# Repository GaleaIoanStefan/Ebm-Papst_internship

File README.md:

# Ebm-Papst_internship
This project contains the PCB design for a equipment that measures contact heat transfer rates.

# The Block Diagram of the Project

In here we can see the main parts of the project namely the supply, a feedback control loop of the ventilator and another feedback control loop of the metal plate. Everything that is contained in the colored frame sits on the actual PCB.

An Arduino Nano Esp32 microcontroller is the brain of the board, which will control the speed of the fan on the left of the schematic with a voltage switch, through a Hall speed sensor to complete a feedback loop. Similarly, on the right side, the esp32 will control the temperature of a hob with a 120W resistor with a voltage switch, and the feedback communication is done by 2 NTC thermistors

The tool used in this project was KiCad 9.0

# The electrical schematic of the PCB

# The layout of the PCB

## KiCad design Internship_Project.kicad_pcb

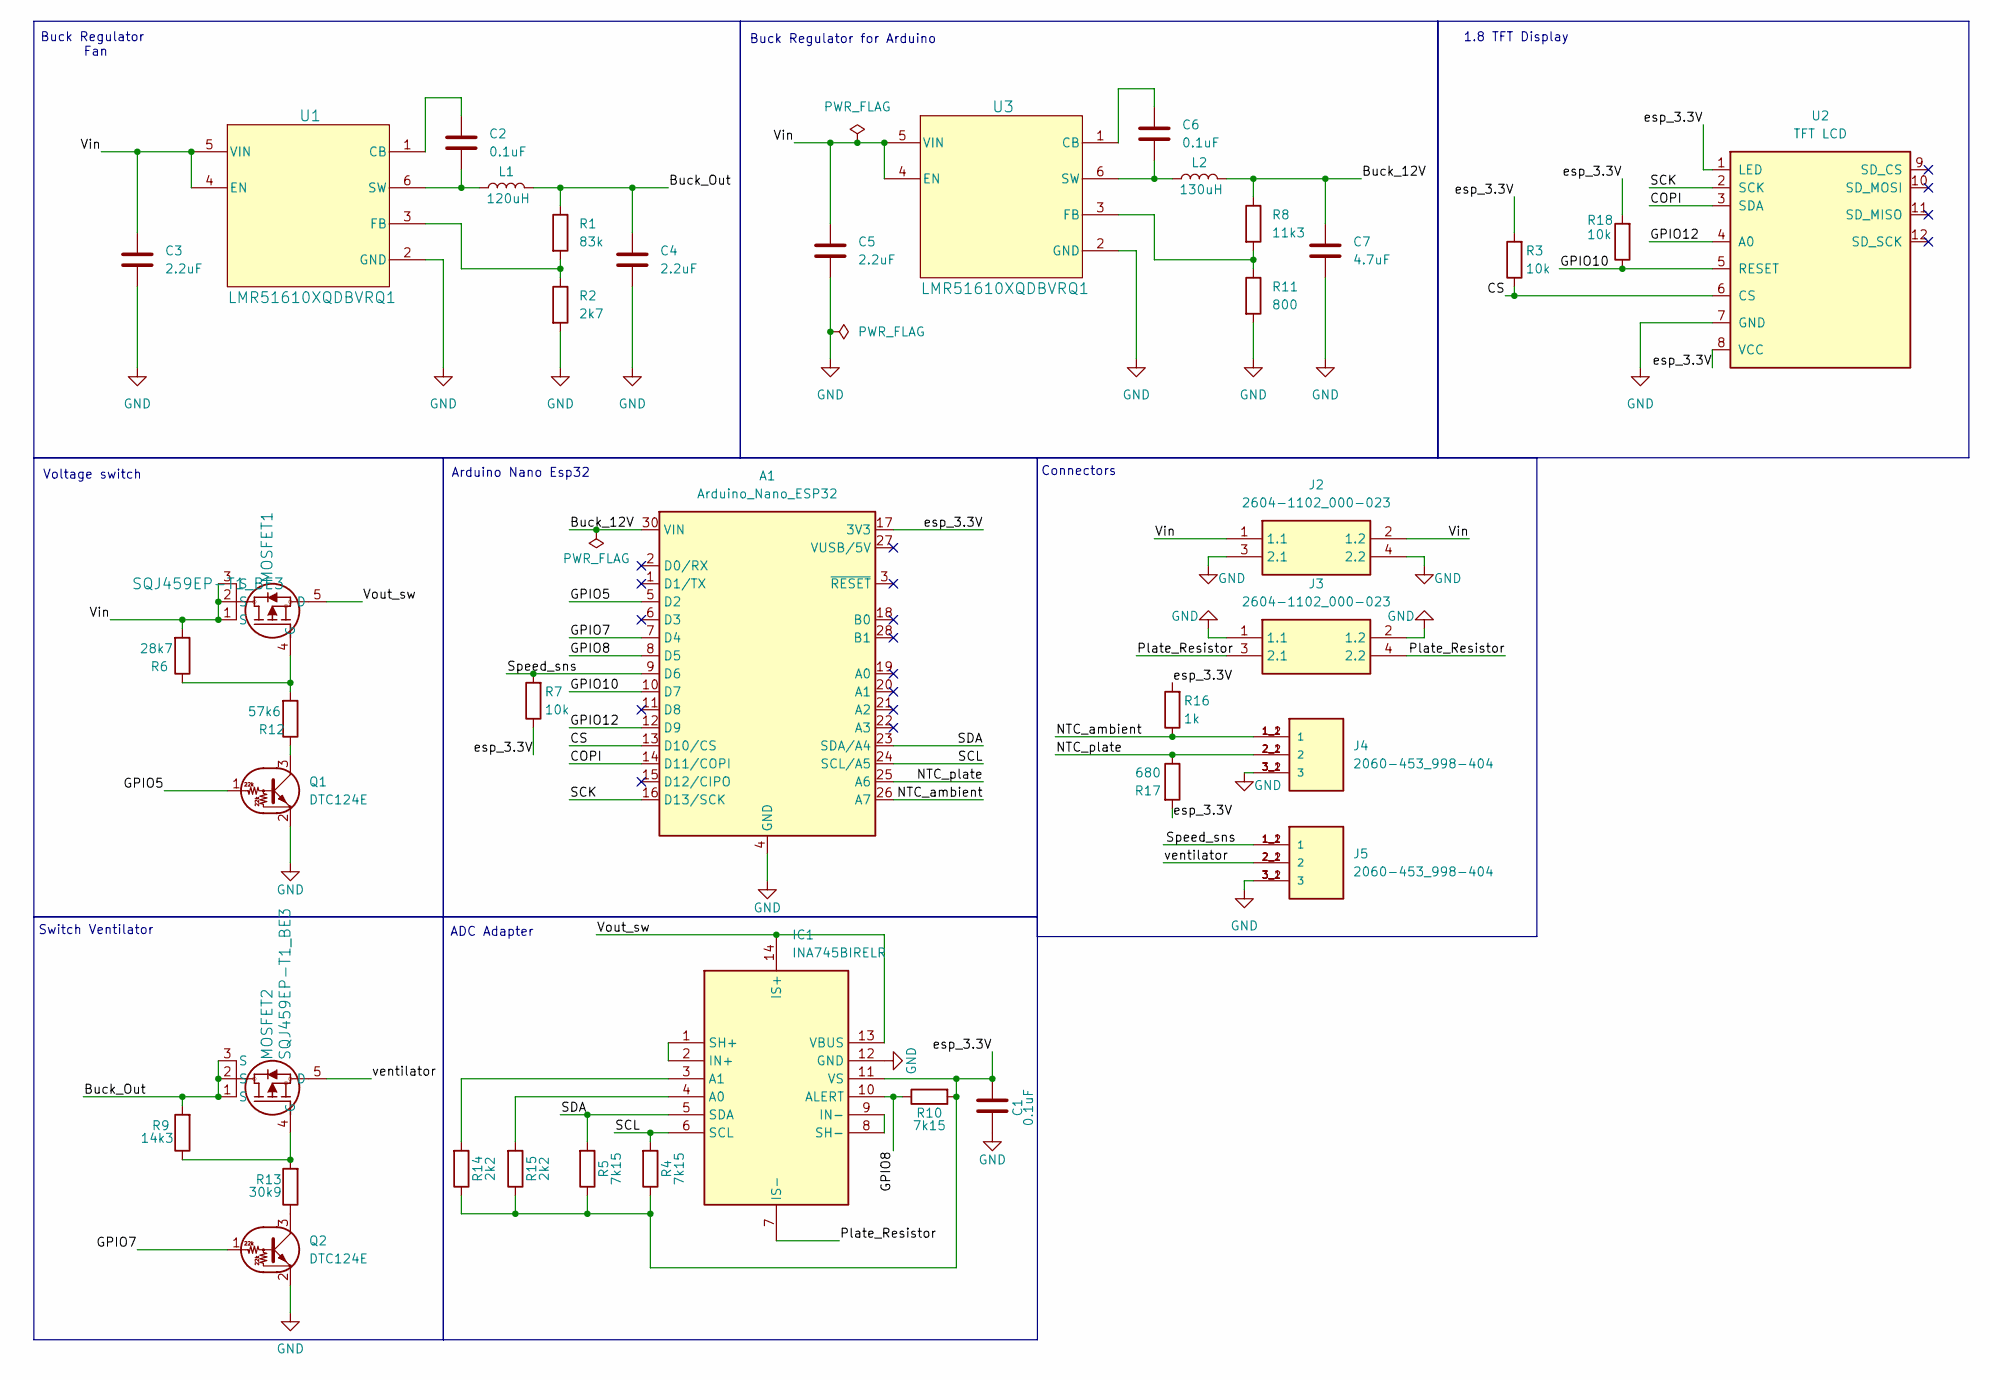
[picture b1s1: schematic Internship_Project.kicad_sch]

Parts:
A1: Arduino_Nano_ESP32; Arduino_Nano_WithMountingHoles
C1, C2, C6: 0.1uF; C_0805_2012Metric
C3, C4, C5: 2.2uF; C_1206_3216Metric
C7: 4.7uF; C_1206_3216Metric
IC1: INA745BIRELR; Manufacturer_Part_Number INA745BIRELR; Mouser Part Number 595-INA745BIRELR
J2, J3: 2604-1102_000-023; 26041102000023; Manufacturer_Part_Number 2604-1102/000-023
J4, J5: 2060-453_998-404; WAGO_2060-453_998-404; PARTREV N/A
L1: 120uH; L_1210_3225Metric
L2: 130uH; L_1210_3225Metric
MOSFET1, MOSFET2: SQJ459EP-T1_BE3; TO_0EP-T1_BE3_VIS
Q1, Q2: DTC124E; SOT-23
R1: 83k; R_0603_1608Metric
R2: 2k7; R_0603_1608Metric
R3, R7, R18: 10k; R_0603_1608Metric
R4, R5, R10: 7k15; R_0603_1608Metric
R6: 28k7; R_0603_1608Metric
R8: 11k3; R_0603_1608Metric
R9: 14k3; R_0603_1608Metric
R11: 800; R_0603_1608Metric
R12: 57k6; R_0603_1608Metric
R13: 30k9; R_0603_1608Metric
R14, R15: 2k2; R_0603_1608Metric
R16: 1k; R_0603_1608Metric
R17: 680; R_0603_1608Metric
U1, U3: LMR51610XQDBVRQ1; DBV0006A-IPC_A
U2: TFT LCD; TFT LCD 1.8inch 128x160 w_ SD Card Slot

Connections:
/Buck_12V: A1.30 (VIN), C7.1, L2.2, R8.1
/Buck_Out: C4.1, L1.2, MOSFET2.1 (S), MOSFET2.2 (S), MOSFET2.3 (S), R1.1, R9.2
/COPI: A1.14 (D11/COPI), U2.3 (SDA)
/CS: A1.13 (D10/CS), R3.1, U2.6 (CS)
/GPIO5: A1.5 (D2), Q1.1 (B)
/GPIO7: A1.7 (D4), Q2.1 (B)
/GPIO8: A1.8 (D5), IC1.10 (ALERT), R10.1
/GPIO10: A1.10 (D7), R18.1, U2.5 (RESET)
/GPIO12: A1.12 (D9), U2.4 (A0)
/NTC_ambient: A1.26 (A7), J4.1_1 (1), J4.1_2 (1), R16.1
/NTC_plate: A1.25 (A6), J4.2_1 (2), J4.2_2 (2), R17.1
/Plate_Resistor: IC1.7 (IS-), J3.3 (2.1), J3.4 (2.2)
/SCK: A1.16 (D13/SCK), U2.2 (SCK)
/SCL: A1.24 (SCL/A5), IC1.6 (SCL), R4.2
/SDA: A1.23 (SDA/A4), IC1.5 (SDA), R5.2
/Speed_sns: A1.9 (D6), J5.1_1 (1), J5.1_2 (1), R7.2
/Vin: C3.1, C5.1, J2.1 (1.1), J2.2 (1.2), MOSFET1.1 (S), MOSFET1.2 (S), MOSFET1.3 (S), R6.2, U1.4 (EN), U1.5 (VIN), U3.4 (EN), U3.5 (VIN)
/Vout_sw: IC1.13 (VBUS), IC1.14 (IS+), MOSFET1.5 (D)
/esp_3.3V: A1.17 (3V3), C1.1, IC1.11 (VS), R3.2, R4.1, R5.1, R7.1, R10.2, R14.1, R15.1, R16.2, R17.2, R18.2, U2.1 (LED), U2.8 (VCC)
/ventilator: J5.2_1 (2), J5.2_2 (2), MOSFET2.5 (D)
GND: A1.4 (GND), A1.29 (GND), C1.2, C3.2, C4.2, C5.2, C7.2, IC1.12 (GND), J2.3 (2.1), J2.4 (2.2), J3.1 (1.1), J3.2 (1.2), J4.3_1 (3), J4.3_2 (3), J5.3_1 (3), J5.3_2 (3), Q1.2 (E), Q2.2 (E), R2.2, R11.2, U1.2 (GND), U2.7 (GND), U3.2 (GND)
unnamed: IC1.4 (A0), R15.2
unnamed: IC1.3 (A1), R14.2
unnamed: IC1.1 (SH+), IC1.2 (IN+)
unnamed: IC1.8 (SH-), IC1.9 (IN-)
unnamed: MOSFET1.4 (G), R6.1, R12.2
unnamed: MOSFET2.4 (G), R9.1, R13.2
unnamed: Q1.3 (C), R12.1
unnamed: Q2.3 (C), R13.1
unnamed: C2.1, U1.1 (CB)
unnamed: R1.2, R2.1, U1.3 (FB)
unnamed: C2.2, L1.1, U1.6 (SW)
unnamed: C6.1, U3.1 (CB)
unnamed: R8.2, R11.1, U3.3 (FB)
unnamed: C6.2, L2.1, U3.6 (SW)

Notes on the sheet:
Buck Regulator Fan
1.8 TFT Display
Switch Ventilator
ADC Adapter
Arduino Nano Esp32
Voltage switch
Connectors
Buck Regulator for Arduino

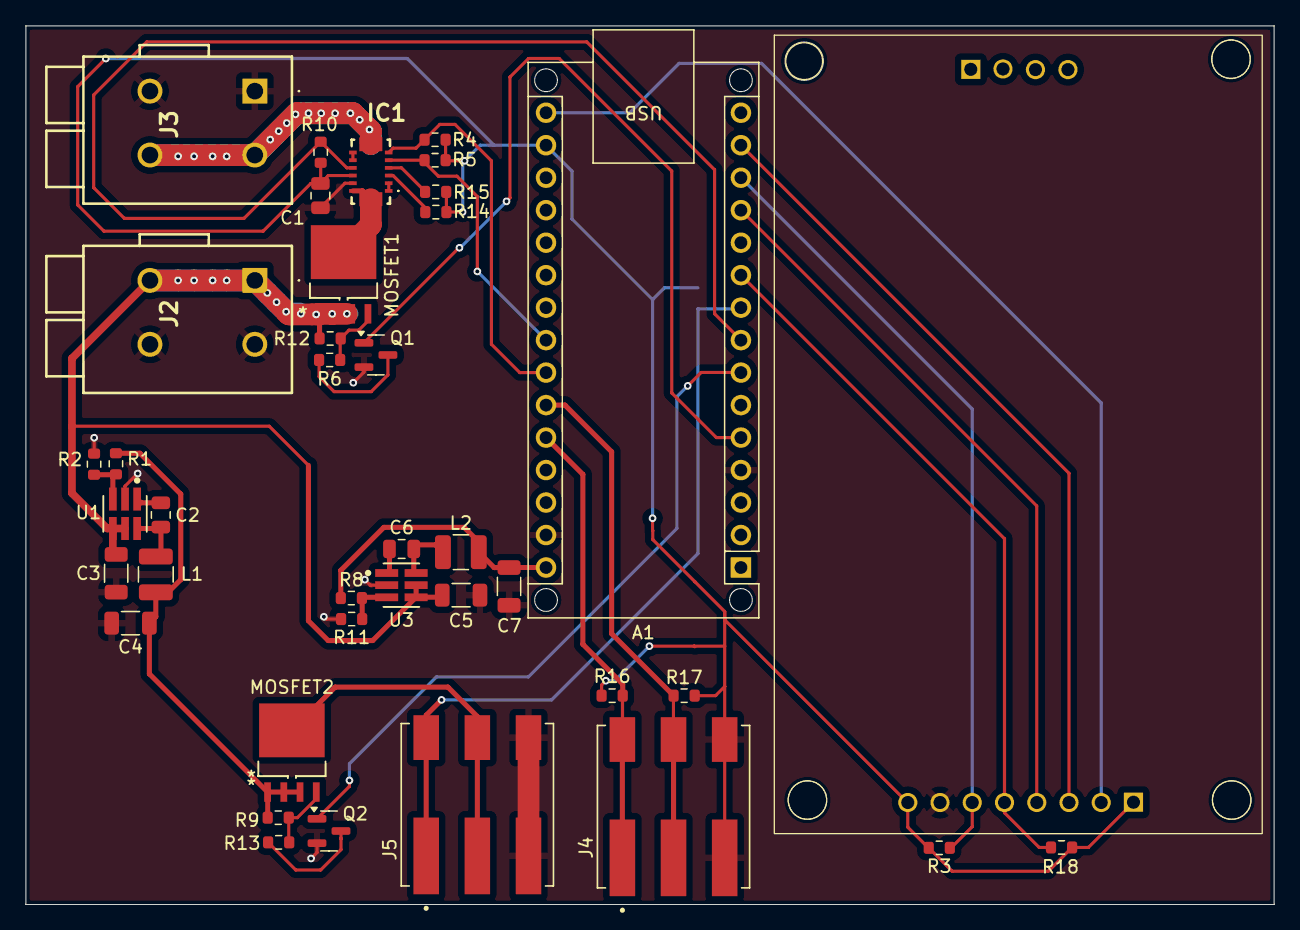
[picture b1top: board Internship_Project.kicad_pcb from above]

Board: 2 copper layers, 97.6 x 68.7 mm, 40 parts (1 on the bottom side), 35 nets.

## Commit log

2026-03-29 Enhance README with project description and diagram
    Added a block diagram image and improved project description.
2026-03-29 Update README with project details
    Added sections about the block diagram and main components.
2026-03-29 Update README with block diagram image
    Added a block diagram image to the README file.
2026-03-29 Fix formatting of section headers in README.md
2026-03-29 Update README with PCB layout information
    Added PCB layout section and image to README.
2026-03-29 Document tool used in project as KiCad 9.0
    Added information about the tool used for the project.
2026-03-29 Update PCB schematic image in README
